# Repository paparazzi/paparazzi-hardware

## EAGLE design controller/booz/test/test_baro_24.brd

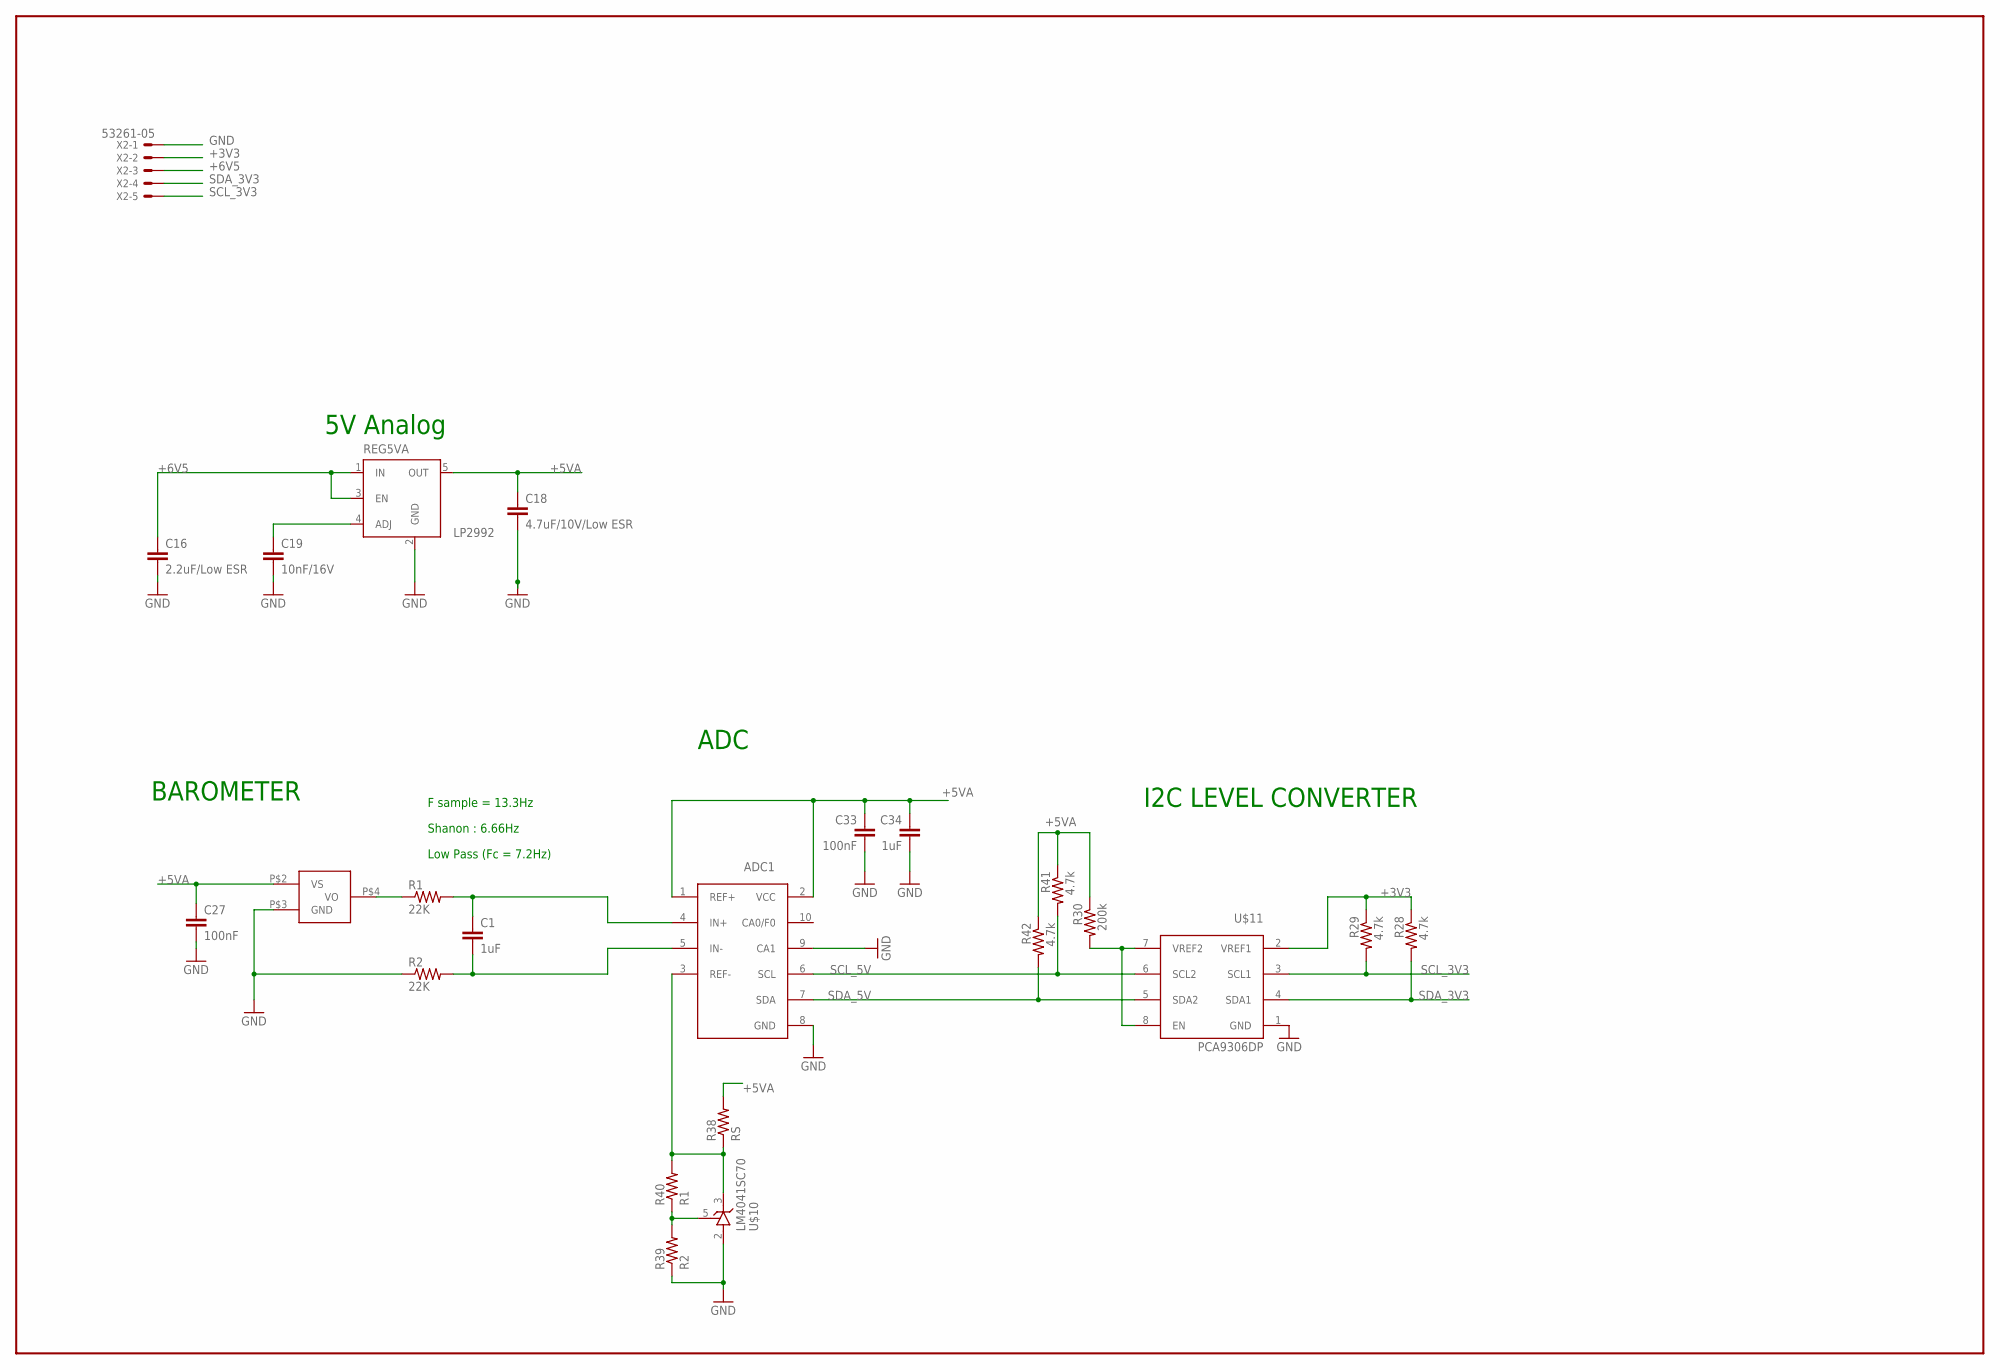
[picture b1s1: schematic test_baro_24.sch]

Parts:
ADC1: LTC2485; DFN10
C1: 1uF; C1206K
C16: 2.2uF/Low ESR; C0603
C18: 4.7uF/10V/Low ESR; C0805K
C19: 10nF/16V; C0603K
C27, C33: 100nF; C0603
C34: 1uF; C0805
R1, R2: 22K; R0603
R28, R29, R41, R42: 4.7k; R0603
R30: 200k; R0603
R38: RS; R0603
R39: R2; R0603
R40: R1; R0603
REG5VA: LP2992; SOT23-5
U$2: MPX6115; CASE_1317
U$10: LM4041SC70; SC70-5L
U$11: PCA9306DP; TSSOP_B3
X2: 53261-05

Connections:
+3V3: R28.1, R29.1, U$11.2 (VREF1), X2.2
+5VA: ADC1.1 (REF+), ADC1.2 (VCC), C18.1, C27.1, C33.1, C34.1, R30.1, R38.2, R41.1, R42.1, REG5VA.5 (OUT), U$2.P$2 (VS)
+6V5: C16.1, REG5VA.1 (IN), REG5VA.3 (EN), X2.3
GND: ADC1.8 (GND), ADC1.9 (CA1), C16.2, C18.2, C19.2, C27.2, C33.2, C34.2, R2.1, R39.1, REG5VA.2 (GND), U$2.P$3 (GND), U$10.2 (A), U$11.1 (GND), X2.1
unnamed: R1.1, U$2.P$4 (VO)
unnamed: ADC1.4 (IN+), C1.1, R1.2
unnamed: ADC1.5 (IN-), C1.2, R2.2
unnamed: R30.2, U$11.7 (VREF2), U$11.8 (EN)
unnamed: R39.2, R40.1, U$10.5 (R)
unnamed: C19.1, REG5VA.4 (ADJ)
unnamed: ADC1.3 (REF-), R38.1, R40.2, U$10.3 (C)
SCL_3V3: R29.2, U$11.3 (SCL1), X2.5
SCL_5V: ADC1.6 (SCL), R41.2, U$11.6 (SCL2)
SDA_3V3: R28.2, U$11.4 (SDA1), X2.4
SDA_5V: ADC1.7 (SDA), R42.2, U$11.5 (SDA2)

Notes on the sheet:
BAROMETER
Low Pass (Fc = 7.2Hz)
F sample = 13.3Hz
Shanon : 6.66Hz
5V Analog
I2C LEVEL CONVERTER
ADC

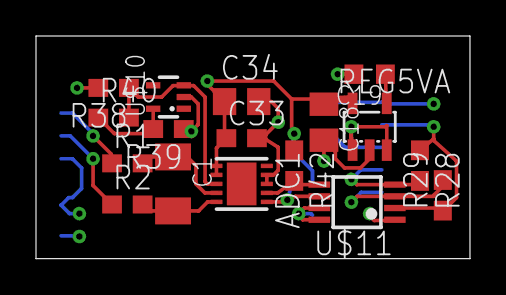
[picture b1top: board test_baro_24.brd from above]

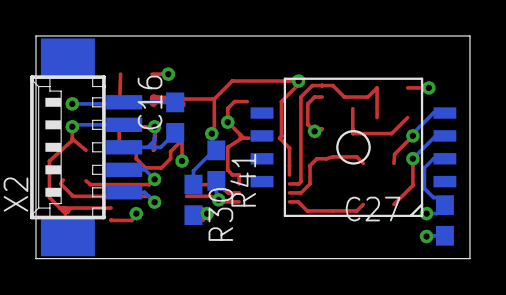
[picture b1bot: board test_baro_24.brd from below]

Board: 2 copper layers, 24.1 x 12.4 mm, 23 parts (6 on the bottom side), 15 nets.

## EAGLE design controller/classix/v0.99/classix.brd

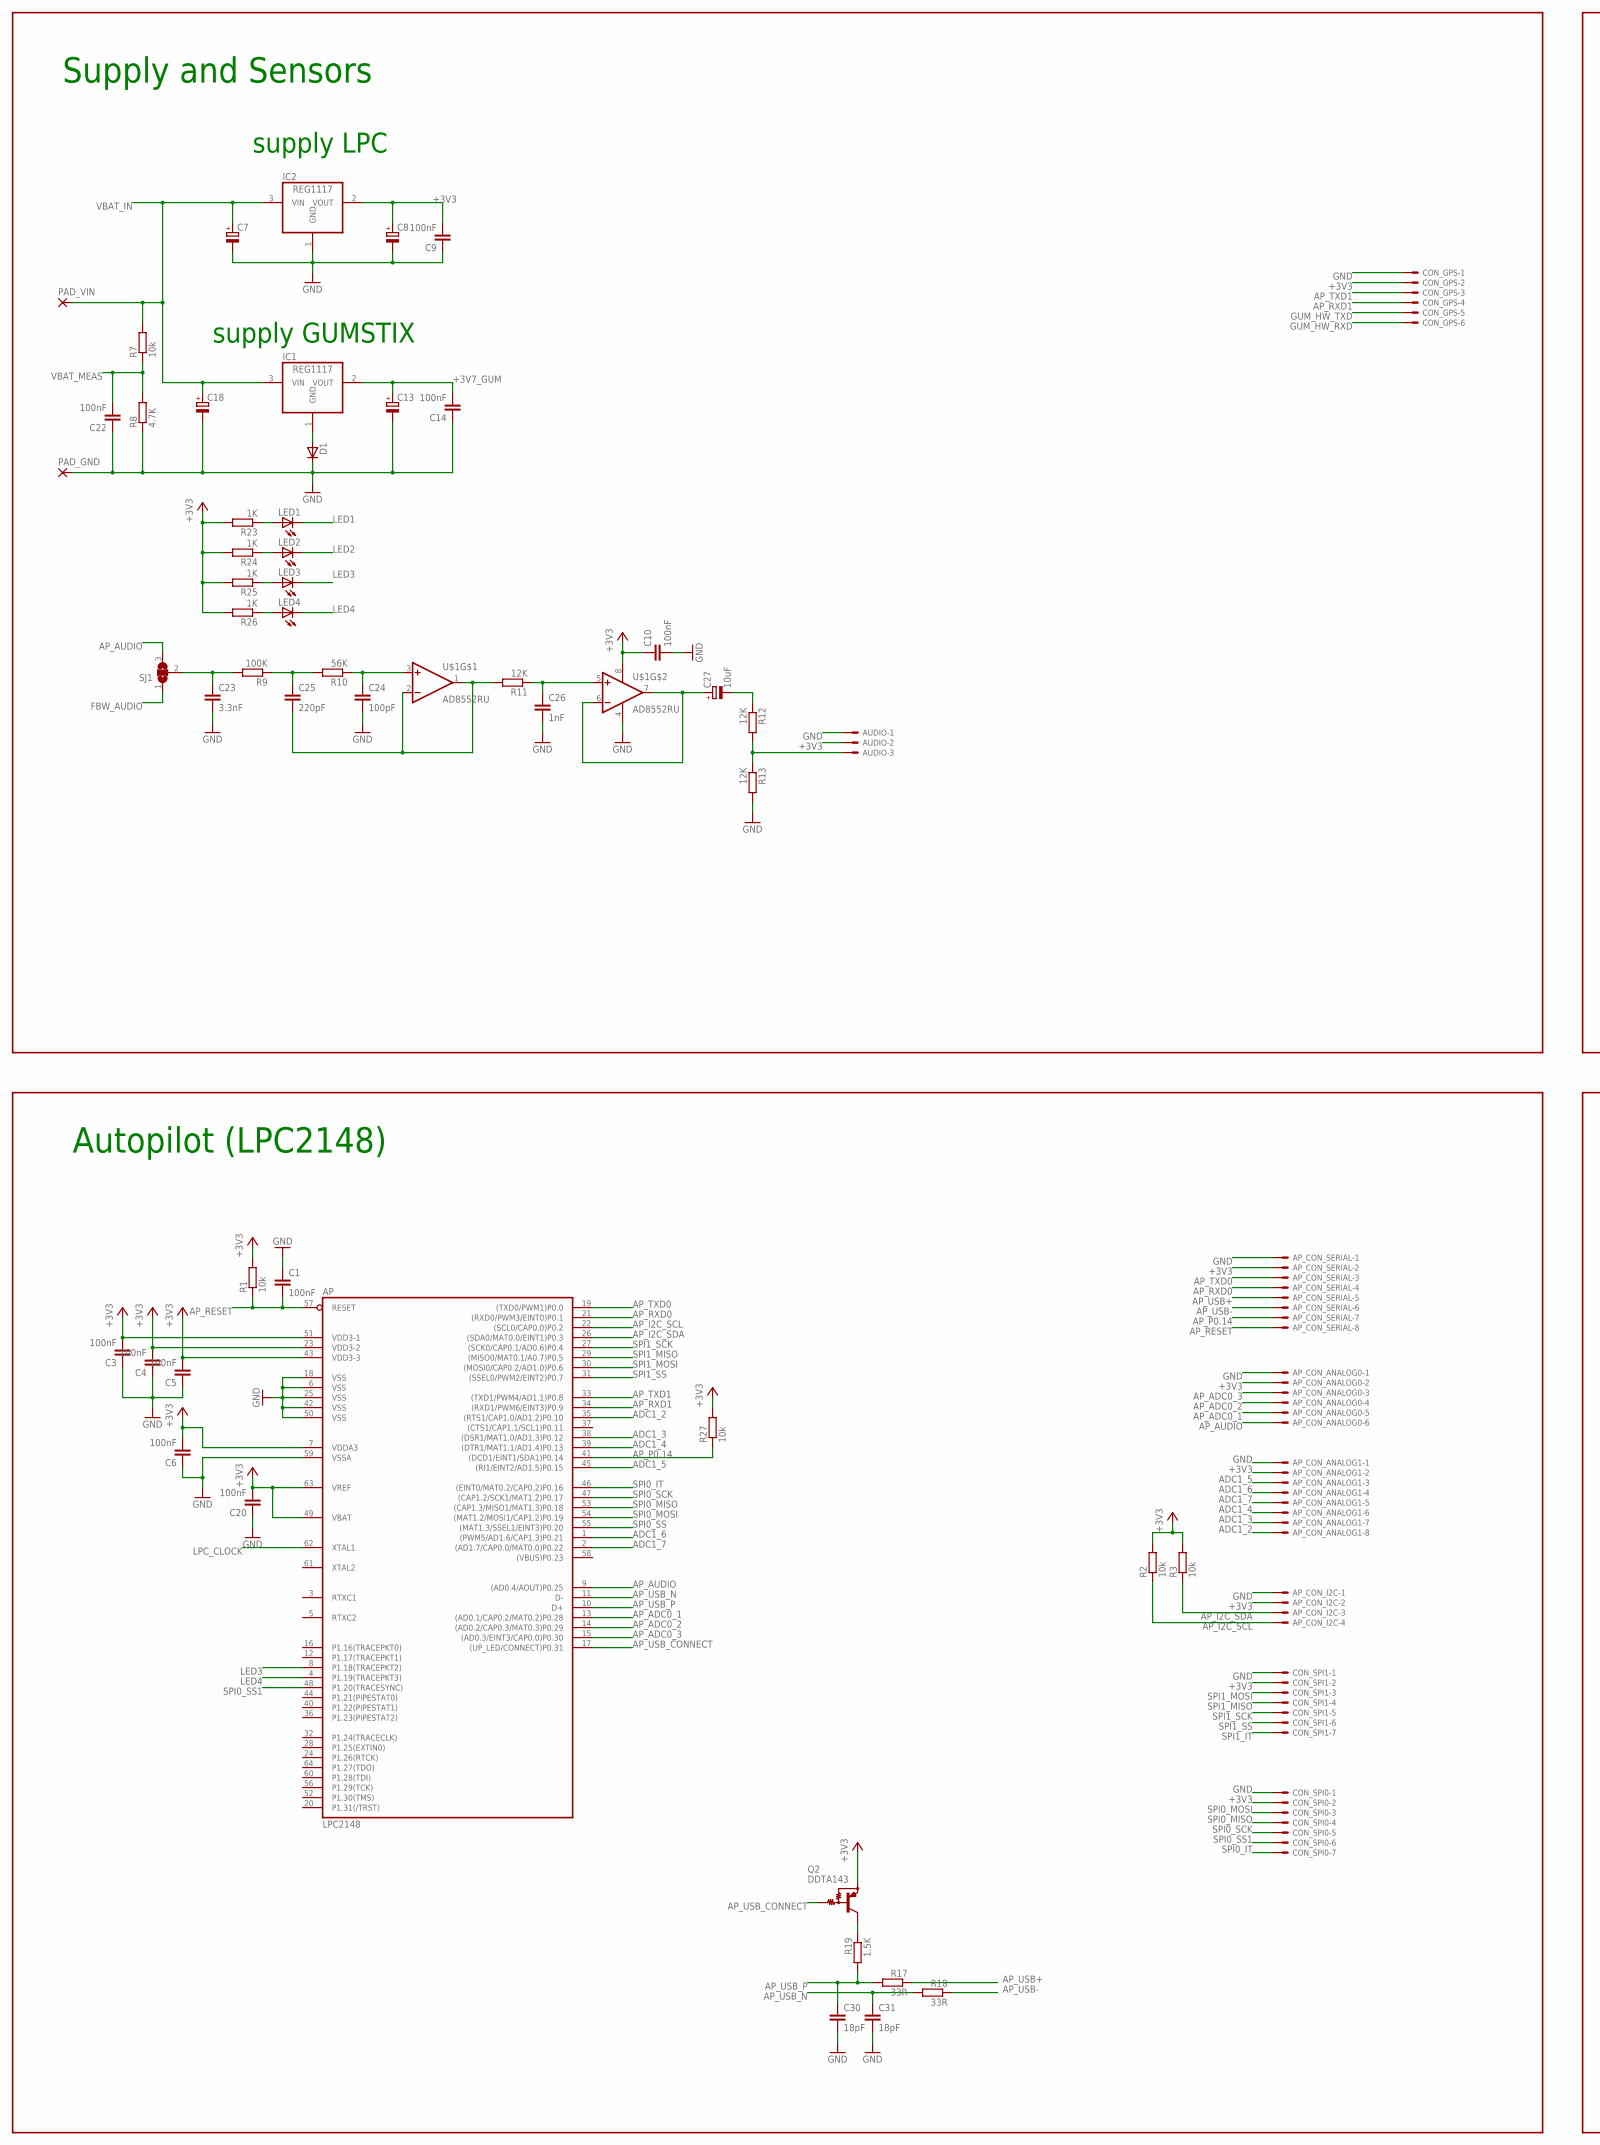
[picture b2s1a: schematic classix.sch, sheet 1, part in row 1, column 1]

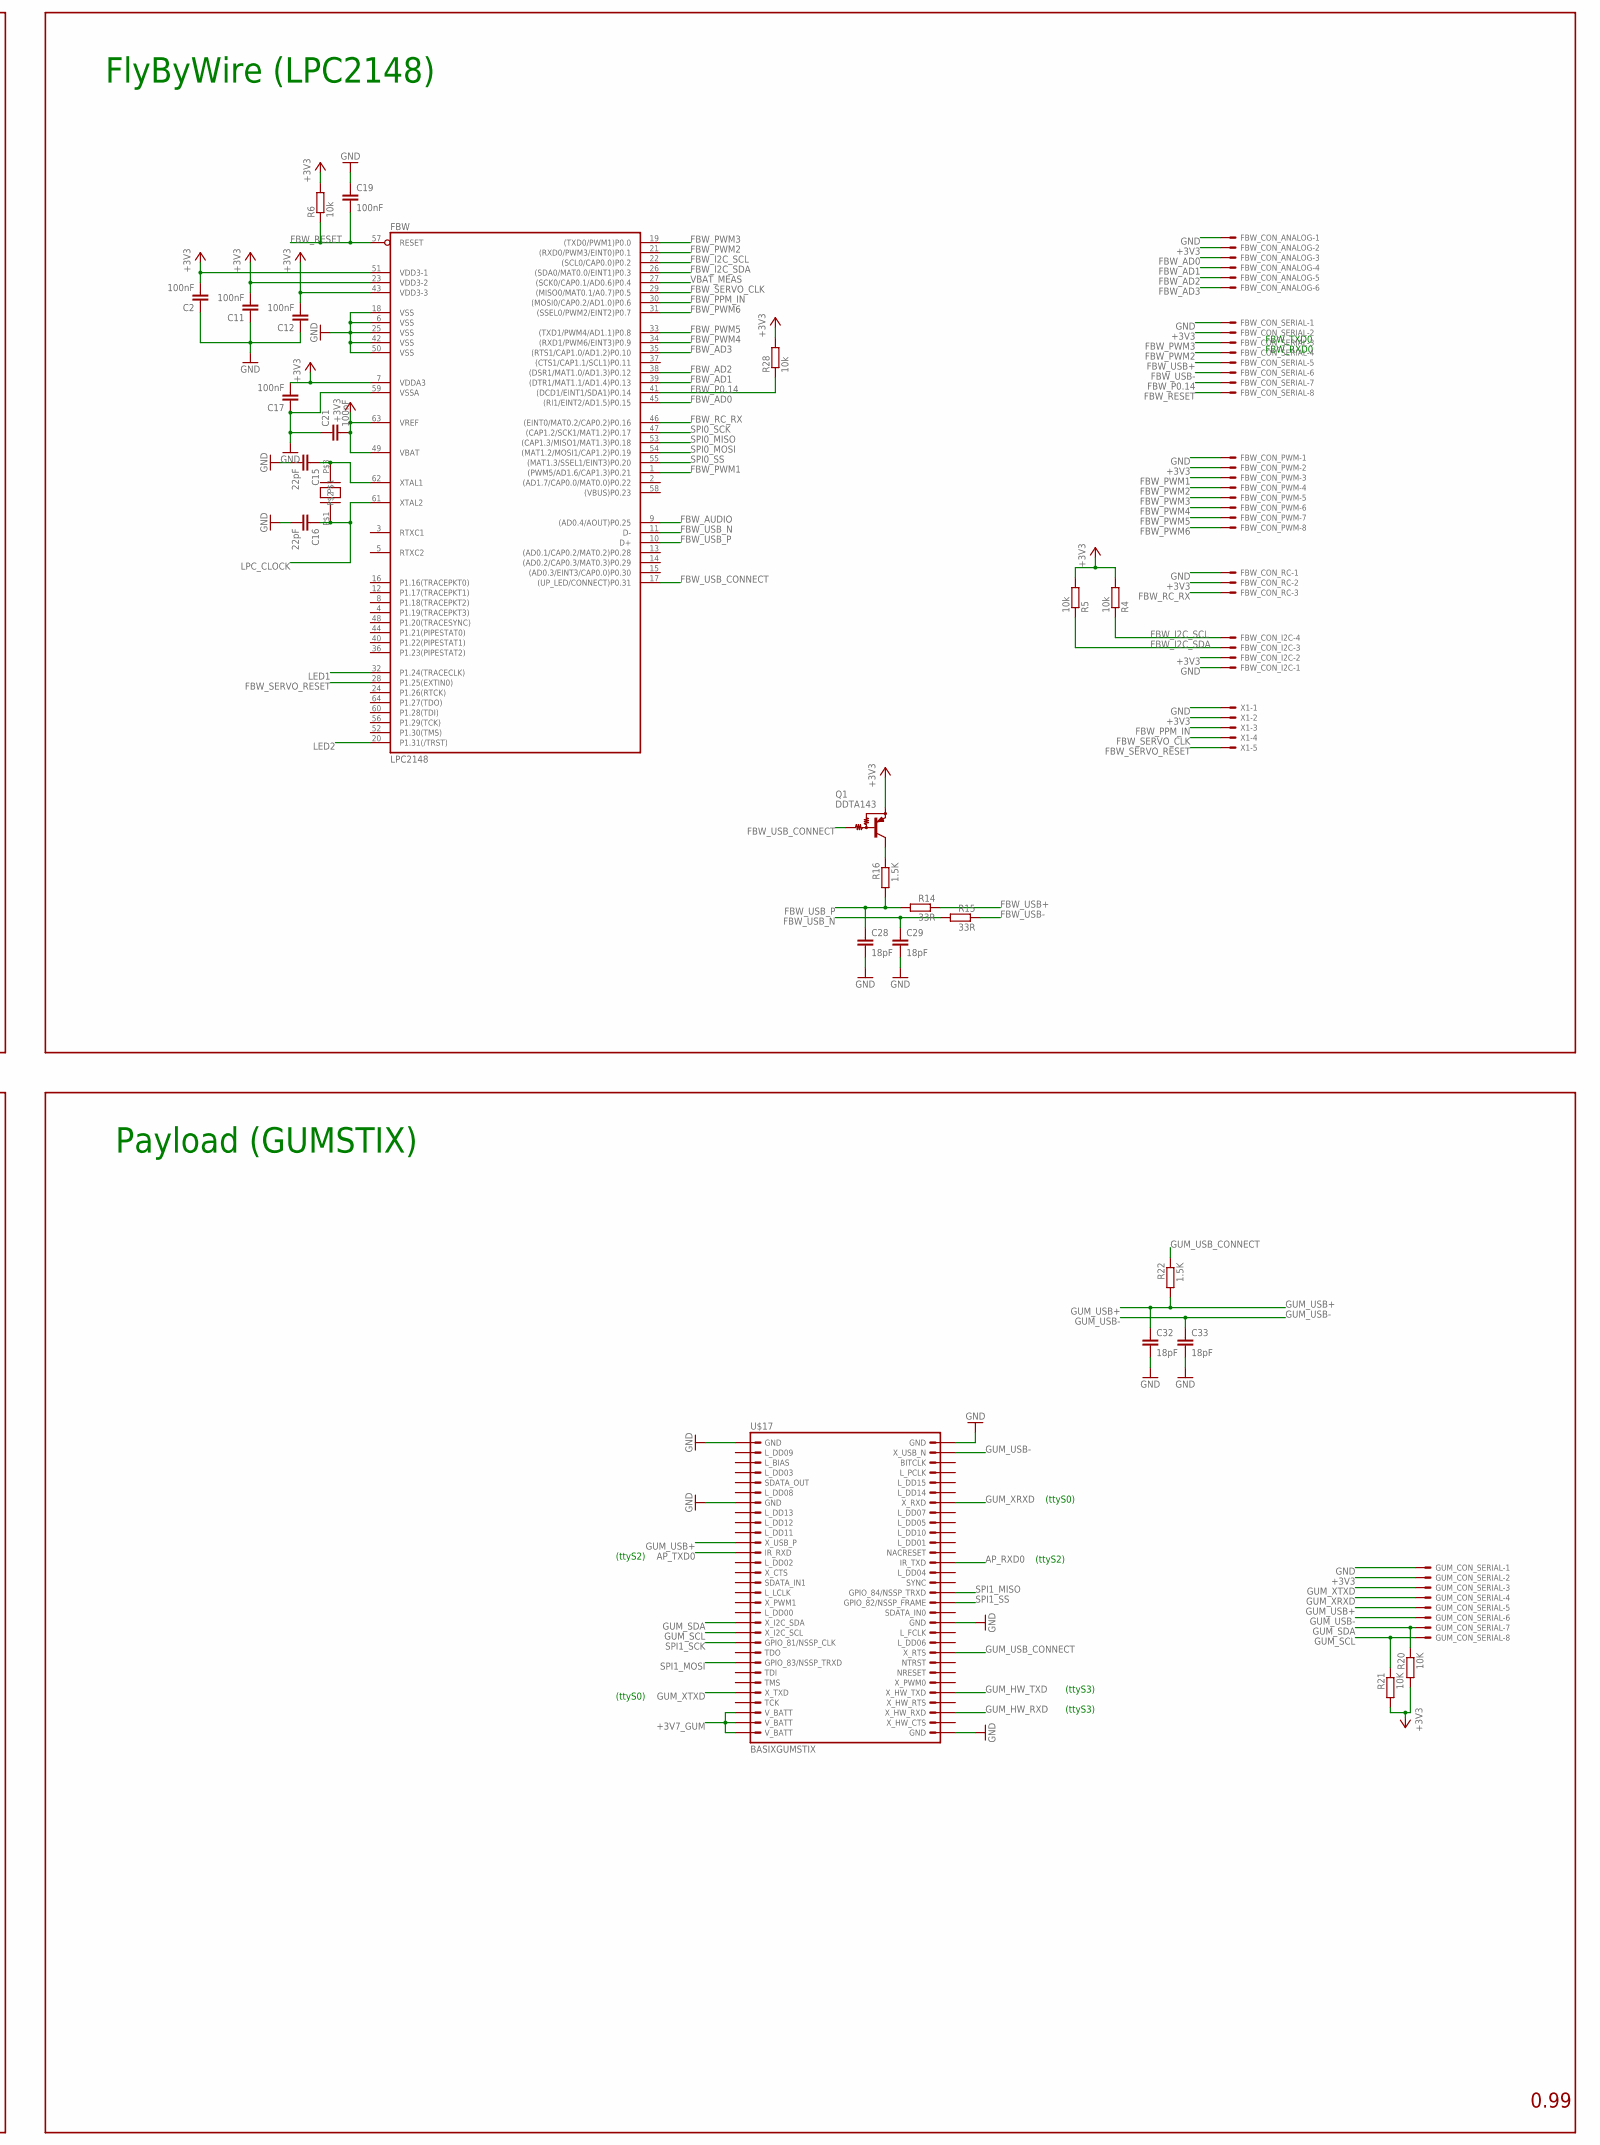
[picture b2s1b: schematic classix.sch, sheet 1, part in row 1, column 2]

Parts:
AP: LPC2148; SQFP-S-10X10-64
AP_CON_ANALOG0: 53047-06
AP_CON_ANALOG1: 53047-08
AP_CON_I2C: 53047-04
AP_CON_SERIAL: 53047-08
AUDIO: 53047-03
C1, C2, C3, C4, C5, C6, C9, C10, C11, C12, C14, C17, C19, C20, C21, C22: 100nF; C0603
C7, C18: CPOL-EUA/3216-18R; A/3216-18R
C8, C13: CPOL-EUB/3528-21R; B/3528-21R
C15, C16: 22pF; C0603
C23: 3.3nF; C0603
C24: 100pF; C0603
C25: 220pF; C0603
C26: 1nF; C0603
C27: 10uF; A/3216-18R
C28, C29, C30, C31, C32, C33: 18pF; C0603
CON_GPS: 53047-06
CON_SPI0, CON_SPI1: 53047-07
D1: D-SOD-80; SOD80
FBW: LPC2148; SQFP-S-10X10-64
FBW_CON_ANALOG: 53047-06
FBW_CON_I2C: 53047-04
FBW_CON_PWM: 53047-08
FBW_CON_RC: 53047-03
FBW_CON_SERIAL: 53047-08
GUM_CON_SERIAL: 53047-08
IC1, IC2: REG1117; SOT223
LED1, LED2, LED3, LED4: LEDCHIP-LED0805; CHIP-LED0805
PAD_GND: SMD5
PAD_VIN: SMD5
Q1, Q2: DDTA143; SC59-BEC
R1, R2, R3, R4, R5, R6, R7, R27, R28: 10k; R0603
R8: 4.7K; R0603
R9: 100K; R0603
R10: 56K; R0603
R11, R12, R13: 12K; R0603
R14, R15, R17, R18: 33R; R0603
R16, R19, R22: 1.5K; R0603
R20, R21: 10K; R0603
R23, R24, R25, R26: 1K; R0603
SJ1: SJ2W; SJ_2
U$1: AD8552RU; TSSOP8
U$17: BASIXGUMSTIX; GUMDF12
U$20: CRYSTAL_CTS; CTS_CRYSTAL
X1: 53047-05

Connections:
+3V3: AP.7 (VDDA3), AP.23 (VDD3-2), AP.43 (VDD3-3), AP.49 (VBAT), AP.51 (VDD3-1), AP.63 (VREF), AP_CON_ANALOG0.2, AP_CON_ANALOG1.2, AP_CON_I2C.2, AP_CON_SERIAL.2, AUDIO.2, C2.2, C3.2, C4.2, C5.2, C6.2, C8.+, C9.2, C10.1, C11.2, C12.2, C17.2, C20.2, C21.2, CON_GPS.2, CON_SPI0.2, CON_SPI1.2, FBW.7 (VDDA3), FBW.23 (VDD3-2), FBW.43 (VDD3-3), FBW.49 (VBAT), FBW.51 (VDD3-1), FBW.63 (VREF), FBW_CON_ANALOG.2, FBW_CON_I2C.2, FBW_CON_PWM.2, FBW_CON_RC.2, FBW_CON_SERIAL.2, GUM_CON_SERIAL.2, IC2.2 (VOUT), Q1.E, Q2.E, R1.2, R2.2, R3.2, R4.2, R5.2, R6.2, R20.2, R21.2, R23.2, R24.2, R25.2, R26.2, R27.2, R28.2, U$1.8 (V+), X1.2
+3V7_GUM: C13.+, C14.2, IC1.2 (VOUT), U$17.28 (V_BATT), U$17.29 (V_BATT), U$17.30 (V_BATT)
ADC1_2: AP.35 ((RTS1/CAP1.0/AD1.2)P0.10), AP_CON_ANALOG1.8
ADC1_3: AP.38 ((DSR1/MAT1.0/AD1.3)P0.12), AP_CON_ANALOG1.7
ADC1_4: AP.39 ((DTR1/MAT1.1/AD1.4)P0.13), AP_CON_ANALOG1.6
ADC1_5: AP.45 ((RI1/EINT2/AD1.5)P0.15), AP_CON_ANALOG1.3
ADC1_6: AP.1 ((PWM5/AD1.6/CAP1.3)P0.21), AP_CON_ANALOG1.4
ADC1_7: AP.2 ((AD1.7/CAP0.0/MAT0.0)P0.22), AP_CON_ANALOG1.5
AP_ADC0_1: AP.13 ((AD0.1/CAP0.2/MAT0.2)P0.28), AP_CON_ANALOG0.5
AP_ADC0_2: AP.14 ((AD0.2/CAP0.3/MAT0.3)P0.29), AP_CON_ANALOG0.4
AP_ADC0_3: AP.15 ((AD0.3/EINT3/CAP0.0)P0.30), AP_CON_ANALOG0.3
AP_AUDIO: AP.9 ((AD0.4/AOUT)P0.25), AP_CON_ANALOG0.6, SJ1.3
AP_I2C_SCL: AP.22 ((SCL0/CAP0.0)P0.2), AP_CON_I2C.4, R2.1
AP_I2C_SDA: AP.26 ((SDA0/MAT0.0/EINT1)P0.3), AP_CON_I2C.3, R3.1
AP_P0.14: AP.41 ((DCD1/EINT1/SDA1)P0.14), AP_CON_SERIAL.7, R27.1
AP_RESET: AP.57 (RESET), AP_CON_SERIAL.8, C1.2, R1.1
AP_RXD0: AP.21 ((RXD0/PWM3/EINT0)P0.1), AP_CON_SERIAL.4, U$17.48 (IR_TXD)
AP_RXD1: AP.34 ((RXD1/PWM6/EINT3)P0.9), CON_GPS.4
AP_TXD0: AP.19 ((TXD0/PWM1)P0.0), AP_CON_SERIAL.3, U$17.12 (IR_RXD)
AP_TXD1: AP.33 ((TXD1/PWM4/AD1.1)P0.8), CON_GPS.3
AP_USB+: AP_CON_SERIAL.5, R17.1
AP_USB-: AP_CON_SERIAL.6, R18.1
AP_USB_CONNECT: AP.17 ((UP_LED/CONNECT)P0.31), Q2.B
AP_USB_N: AP.11 (D-), C31.1, R18.2
AP_USB_P: AP.10 (D+), C30.1, R17.2, R19.2
FBW_AD0: FBW.45 ((RI1/EINT2/AD1.5)P0.15), FBW_CON_ANALOG.3
FBW_AD1: FBW.39 ((DTR1/MAT1.1/AD1.4)P0.13), FBW_CON_ANALOG.4
FBW_AD2: FBW.38 ((DSR1/MAT1.0/AD1.3)P0.12), FBW_CON_ANALOG.5
FBW_AD3: FBW.35 ((RTS1/CAP1.0/AD1.2)P0.10), FBW_CON_ANALOG.6
FBW_AUDIO: FBW.9 ((AD0.4/AOUT)P0.25), SJ1.1
FBW_I2C_SCL: FBW.22 ((SCL0/CAP0.0)P0.2), FBW_CON_I2C.4, R4.1
FBW_I2C_SDA: FBW.26 ((SDA0/MAT0.0/EINT1)P0.3), FBW_CON_I2C.3, R5.1
FBW_P0.14: FBW.41 ((DCD1/EINT1/SDA1)P0.14), FBW_CON_SERIAL.7, R28.1
FBW_PPM_IN: FBW.30 ((MOSI0/CAP0.2/AD1.0)P0.6), X1.3
FBW_PWM1: FBW.1 ((PWM5/AD1.6/CAP1.3)P0.21), FBW_CON_PWM.3
FBW_PWM2: FBW.21 ((RXD0/PWM3/EINT0)P0.1), FBW_CON_PWM.4, FBW_CON_SERIAL.4
FBW_PWM3: FBW.19 ((TXD0/PWM1)P0.0), FBW_CON_PWM.5, FBW_CON_SERIAL.3
FBW_PWM4: FBW.34 ((RXD1/PWM6/EINT3)P0.9), FBW_CON_PWM.6
FBW_PWM5: FBW.33 ((TXD1/PWM4/AD1.1)P0.8), FBW_CON_PWM.7
FBW_PWM6: FBW.31 ((SSEL0/PWM2/EINT2)P0.7), FBW_CON_PWM.8
FBW_RC_RX: FBW.46 ((EINT0/MAT0.2/CAP0.2)P0.16), FBW_CON_RC.3
FBW_RESET: C19.2, FBW.57 (RESET), FBW_CON_SERIAL.8, R6.1
FBW_SERVO_CLK: FBW.29 ((MISO0/MAT0.1/A0.7)P0.5), X1.4
FBW_SERVO_RESET: FBW.28 (P1.25(EXTIN0)), X1.5
FBW_USB+: FBW_CON_SERIAL.5, R14.1
FBW_USB-: FBW_CON_SERIAL.6, R15.1
FBW_USB_CONNECT: FBW.17 ((UP_LED/CONNECT)P0.31), Q1.B
FBW_USB_N: C29.1, FBW.11 (D-), R15.2
FBW_USB_P: C28.1, FBW.10 (D+), R14.2, R16.2
FOO_BAR: C23.1, R9.2, SJ1.2
GND: AP.6 (VSS), AP.18 (VSS), AP.25 (VSS), AP.42 (VSS), AP.50 (VSS), AP.59 (VSSA), AP_CON_ANALOG0.1, AP_CON_ANALOG1.1, AP_CON_I2C.1, AP_CON_SERIAL.1, AUDIO.1, C1.1, C2.1, C3.1, C4.1, C5.1, C6.1, C7.-, C8.-, C9.1, C10.2, C11.1, C12.1, C13.-, C14.1, C15.2, C16.2, C17.1, C18.-, C19.1, C20.1, C21.1, C22.1, C23.2, C24.2, C26.2, C28.2, C29.2, C30.2, C31.2, C32.2, C33.2, CON_GPS.1, CON_SPI0.1, CON_SPI1.1, D1.1 (C), FBW.6 (VSS), FBW.18 (VSS), FBW.25 (VSS), FBW.42 (VSS), FBW.50 (VSS), FBW.59 (VSSA), FBW_CON_ANALOG.1, FBW_CON_I2C.1, FBW_CON_PWM.1, FBW_CON_RC.1, FBW_CON_SERIAL.1, GUM_CON_SERIAL.1, IC2.1 (GND), PAD_GND.1, R8.1, R13.2, U$1.4 (V-), U$17.1 (GND), U$17.7 (GND), U$17.31 (GND), U$17.42 (GND), U$17.60 (GND), X1.1
GUM_HW_RXD: CON_GPS.6, U$17.33 (X_HW_RXD)
GUM_HW_TXD: CON_GPS.5, U$17.35 (X_HW_TXD)
GUM_SCL: GUM_CON_SERIAL.8, R21.1, U$17.20 (X_I2C_SCL)
GUM_SDA: GUM_CON_SERIAL.7, R20.1, U$17.19 (X_I2C_SDA)
GUM_USB+: C32.1, GUM_CON_SERIAL.5, R22.2, U$17.11 (X_USB_P)
GUM_USB-: C33.1, GUM_CON_SERIAL.6, U$17.59 (X_USB_N)
GUM_USB_CONNECT: R22.1, U$17.39 (X_RTS)
GUM_XRXD: GUM_CON_SERIAL.4, U$17.54 (X_RXD)
GUM_XTXD: GUM_CON_SERIAL.3, U$17.26 (X_TXD)
LED1: FBW.32 (P1.24(TRACECLK)), LED1.C
LED2: FBW.20 (P1.31(/TRST)), LED2.C
LED3: AP.8 (P1.18(TRACEPKT2)), LED3.C
LED4: AP.4 (P1.19(TRACEPKT3)), LED4.C
LPC_CLOCK: AP.62 (XTAL1), C16.1, FBW.61 (XTAL2), U$20.P$1
unnamed: C15.1, FBW.62 (XTAL1), U$20.P$3
unnamed: D1.2 (A), IC1.1 (GND)
unnamed: LED4.A, R26.1
unnamed: LED1.A, R23.1
unnamed: LED2.A, R24.1
unnamed: LED3.A, R25.1
unnamed: C25.1, R9.1, R10.2
unnamed: C24.1, R10.1, U$1.3 (+IN)
unnamed: C25.2, R11.2, U$1.1 (OUT), U$1.2 (-IN)
unnamed: C26.1, R11.1, U$1.5 (+IN)
unnamed: C27.+, U$1.6 (-IN), U$1.7 (OUT)
unnamed: C27.-, R12.1
unnamed: AUDIO.3, R12.2, R13.1
unnamed: Q1.C, R16.1
unnamed: Q2.C, R19.1
SPI0_IT: AP.46 ((EINT0/MAT0.2/CAP0.2)P0.16), CON_SPI0.7
SPI0_MISO: AP.53 ((CAP1.3/MISO1/MAT1.3)P0.18), CON_SPI0.4, FBW.53 ((CAP1.3/MISO1/MAT1.3)P0.18)
SPI0_MOSI: AP.54 ((MAT1.2/MOSI1/CAP1.2)P0.19), CON_SPI0.3, FBW.54 ((MAT1.2/MOSI1/CAP1.2)P0.19)
SPI0_SCK: AP.47 ((CAP1.2/SCK1/MAT1.2)P0.17), CON_SPI0.5, FBW.47 ((CAP1.2/SCK1/MAT1.2)P0.17)
SPI0_SS: AP.55 ((MAT1.3/SSEL1/EINT3)P0.20), FBW.55 ((MAT1.3/SSEL1/EINT3)P0.20)
SPI0_SS1: AP.48 (P1.20(TRACESYNC)), CON_SPI0.6
SPI1_IT: CON_SPI1.7
SPI1_MISO: AP.29 ((MISO0/MAT0.1/A0.7)P0.5), CON_SPI1.4, U$17.45 (GPIO_84/NSSP_TRXD)
SPI1_MOSI: AP.30 ((MOSI0/CAP0.2/AD1.0)P0.6), CON_SPI1.3, U$17.23 (GPIO_83/NSSP_TRXD)
SPI1_SCK: AP.27 ((SCK0/CAP0.1/AD0.6)P0.4), CON_SPI1.5, U$17.21 (GPIO_81/NSSP_CLK)
SPI1_SS: AP.31 ((SSEL0/PWM2/EINT2)P0.7), CON_SPI1.6, U$17.44 (GPIO_82/NSSP_FRAME)
VBAT_IN: C7.+, C18.+, IC1.3 (VIN), IC2.3 (VIN), PAD_VIN.1, R7.2
VBAT_MEAS: C22.2, FBW.27 ((SCK0/CAP0.1/AD0.6)P0.4), R7.1, R8.2

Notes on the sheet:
FlyByWire (LPC2148)
Autopilot (LPC2148)
Payload (GUMSTIX)
Supply and Sensors
(ttyS2)
(ttyS3)
(ttyS0)
supply LPC
supply GUMSTIX
FBW_TXD0
FBW_RXD0
0.99

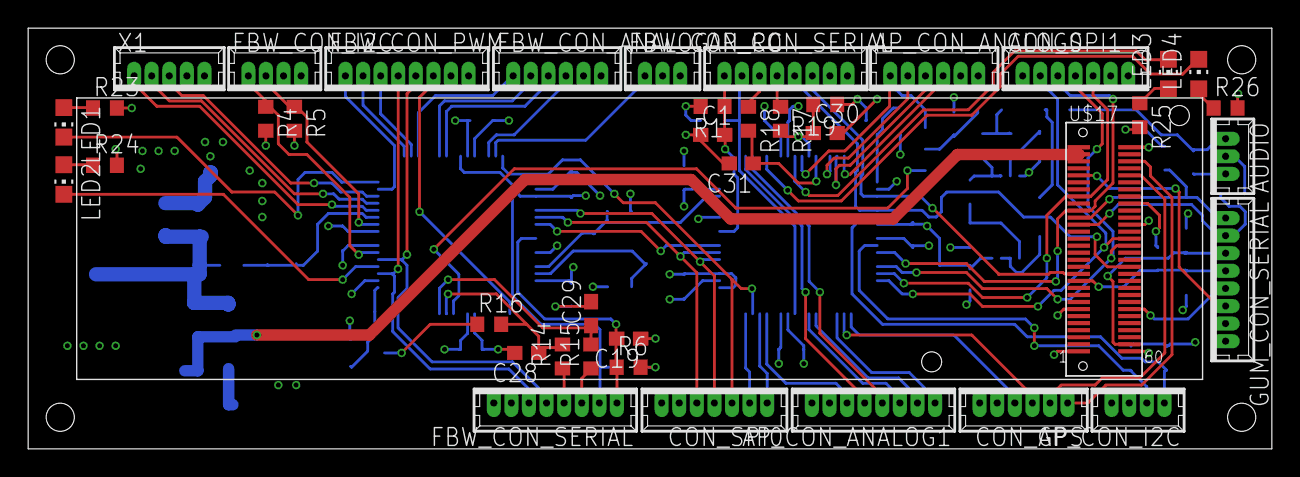
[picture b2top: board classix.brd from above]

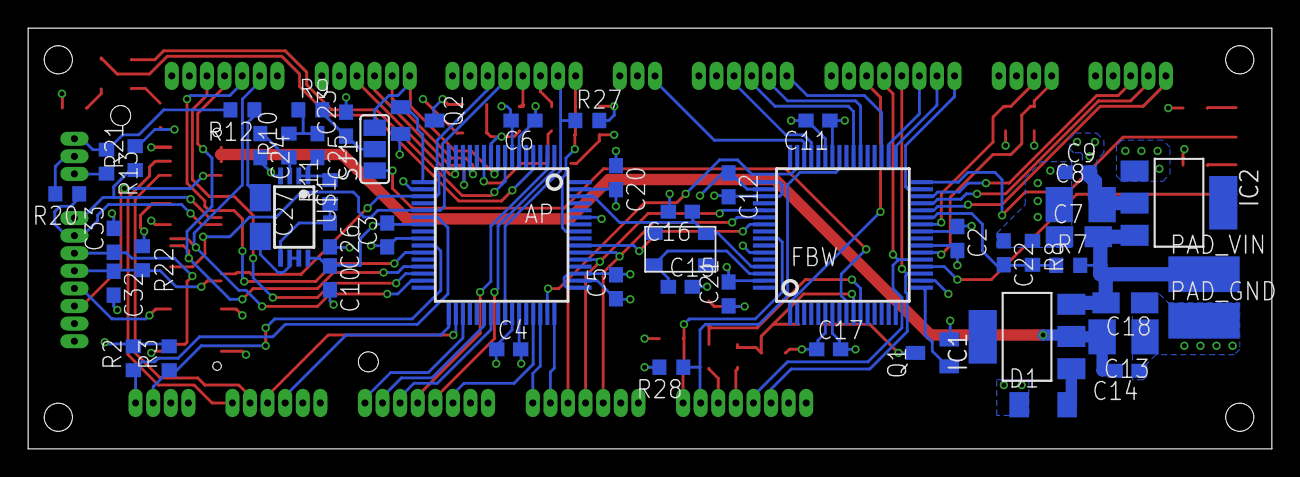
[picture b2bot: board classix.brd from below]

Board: 4 copper layers, 88.4 x 29.9 mm, 93 parts (53 on the bottom side), 92 nets.

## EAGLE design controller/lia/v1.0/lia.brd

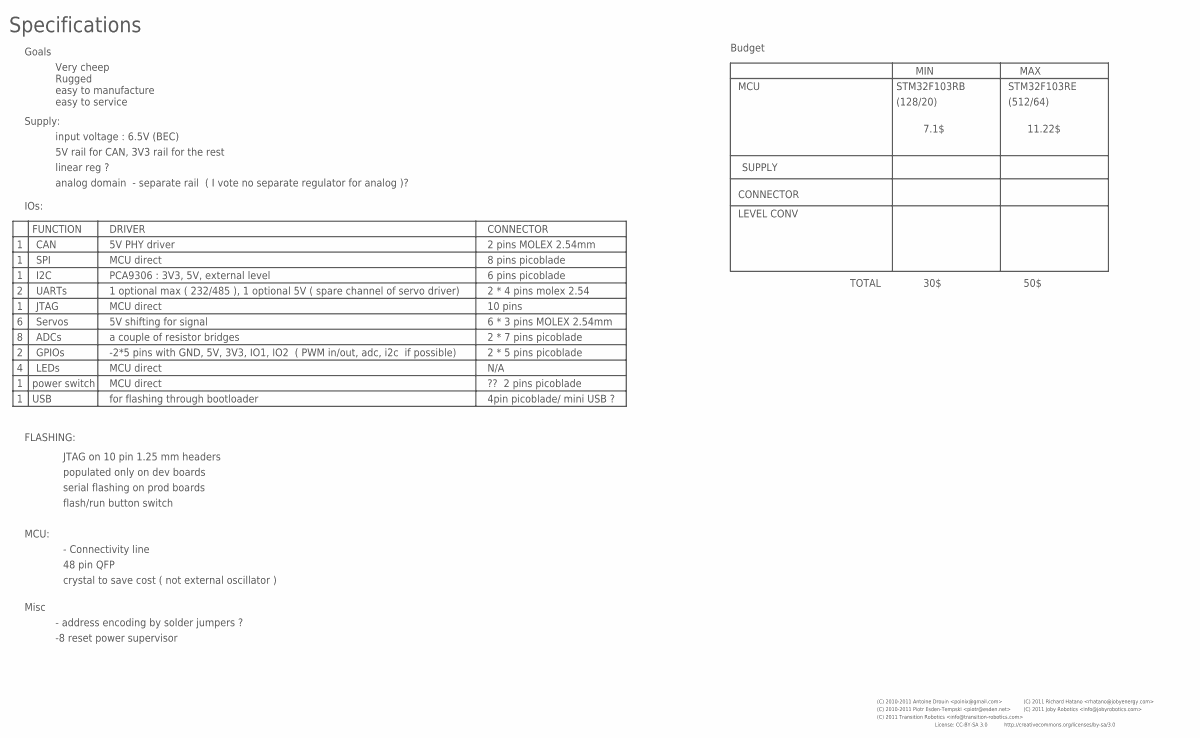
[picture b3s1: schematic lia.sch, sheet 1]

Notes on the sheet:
Specifications
input voltage : 6.5V (BEC)
IOs:
CAN
SPI
I2C
UARTs
Servos
1 optional max ( 232/485 ), 1 optional 5V ( spare channel of servo driver)
5V shifting for signal
FLASHING:
JTAG on 10 pin 1.25 mm headers
populated only on dev boards
serial flashing on prod boards
flash/run button switch
PCA9306 : 3V3, 5V, external level
MCU:
- Connectivity line
48 pin QFP
crystal to save cost ( not external oscillator )
Supply:
5V rail for CAN, 3V3 rail for the rest
linear reg ?
analog domain - separate rail ( I vote no separate regulator for analog )?
Goals
Very cheep
Rugged
easy to manufacture
easy to service
Misc
- address encoding by solder jumpers ?
JTAG
ADCs
-2*5 pins with GND, 5V, 3V3, IO1, IO2 ( PWM in/out, adc, i2c if possible)
LEDs
5V PHY driver
power switch
MCU direct
a couple of resistor bridges
-8 reset power supervisor

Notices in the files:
controller/lia/v1.1/lia.sch:
License: CC-BY-SA 3.0
http://creativecommons.org/licenses/by-sa/3.0
(C) 2010-2011 Piotr Esden-Tempski
(C) 2010-2011 Antoine Drouin
(C) 2011 Richard Hatano
(C) 2011 Joby Robotics
(C) 2011 Transition Robotics
